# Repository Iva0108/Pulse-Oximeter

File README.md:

A pulse oximeter project that consists of hardware, firmware, and software implementation. This project is provided for educational and research purposes only, 
and is NOT authorized for medical use.
This project presents a portable pulse oximeter capable of measuring blood oxygen saturation (SpO₂) and heart rate (BPM) using the MAX30102
sensor. The measured values are displayed on an OLED screen and transmitted wirelessly to an Android application via an HC-05 Bluetooth module.

Features:
- Measurement of SpO₂ (oxygen saturation)
- Measurement of heart rate (BPM)
- Real-time display on SSD1306 OLED (128×64)
- Wireless Bluetooth communication
- Custom KiCad PCB design
- Android application for data visualization
- Powered by a 3.7 V Li-Po battery with charging circuitry

Building the Project:

Android App
The Android application was developed in Java using Android Studio. 
It connects to the HC-05 module via Bluetooth SPP and displays the received BPM and SpO₂ values in real time.
Expected data format:
BPM:72,SPO2:98
- Open Oximeter_App/PulseOxApp in Android Studio.
- Allow Gradle synchronization.
- Build and run the application.

Firmware
The firmware was developed in the Arduino IDE for the STM32 Blue Pill. 
It uses the MAX30105 library to acquire sensor data, calculate heart rate and oxygen saturation, and transmit the values over Bluetooth.
- Open BT_PulseOximeter.ino in the Arduino IDE.
- Select the STM32 board package (if not already installed, install it via Boards Manager).
- Upload the firmware using ST-Link. It might be necessary to use ST Programmer for flashing instead of doing it directly in Arduino IDE, in which case you will need
to select either a .bin or .elf file to do so.

PCB
The custom PCB was designed in KiCad as a two-layer board with separate schematic sheets for power supply, MCU, sensor module, HC-05 Bluetooth module and OLED display.
- Open Oximeter.kicad_pro in KiCad.
- Use the PCB editor or 3D viewer to inspect the design.

Hardware & Firmware:

Android App:

PCB:

Case:

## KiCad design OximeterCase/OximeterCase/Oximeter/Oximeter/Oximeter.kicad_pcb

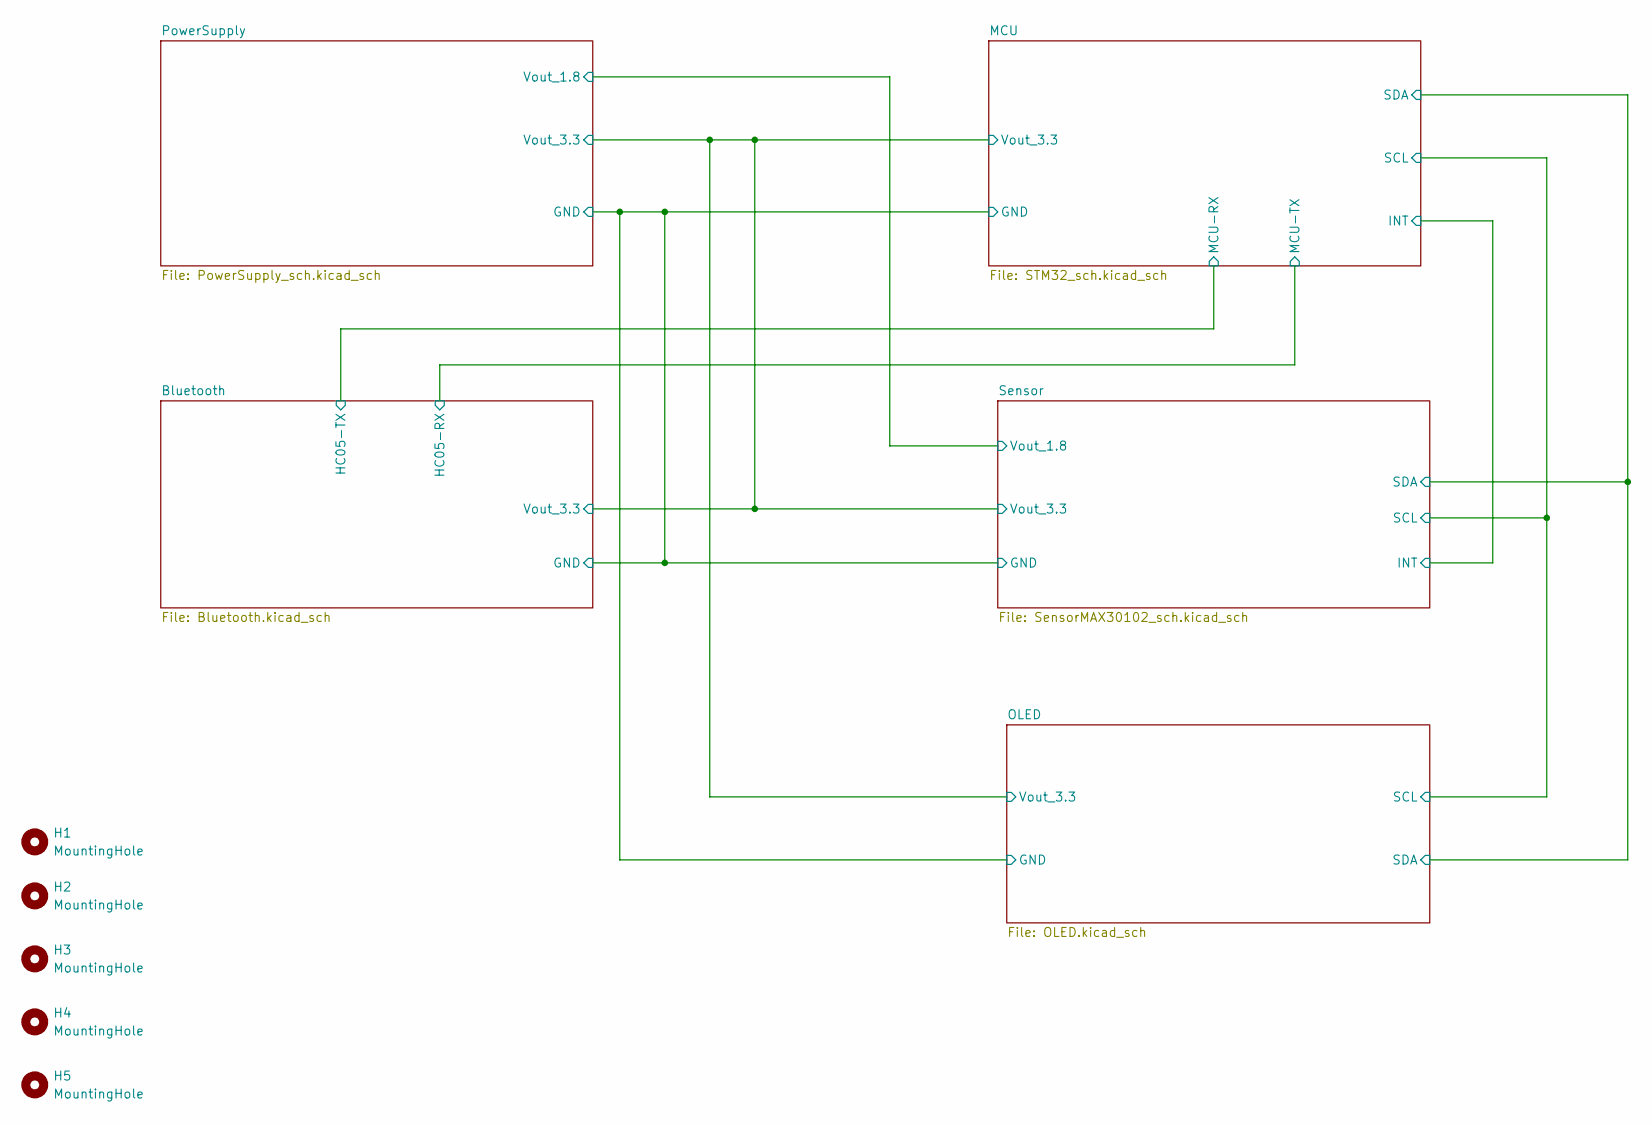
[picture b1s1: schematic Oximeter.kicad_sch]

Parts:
H1, H2, H3, H4, H5: MountingHole; MountingHole_2.2mm_M2

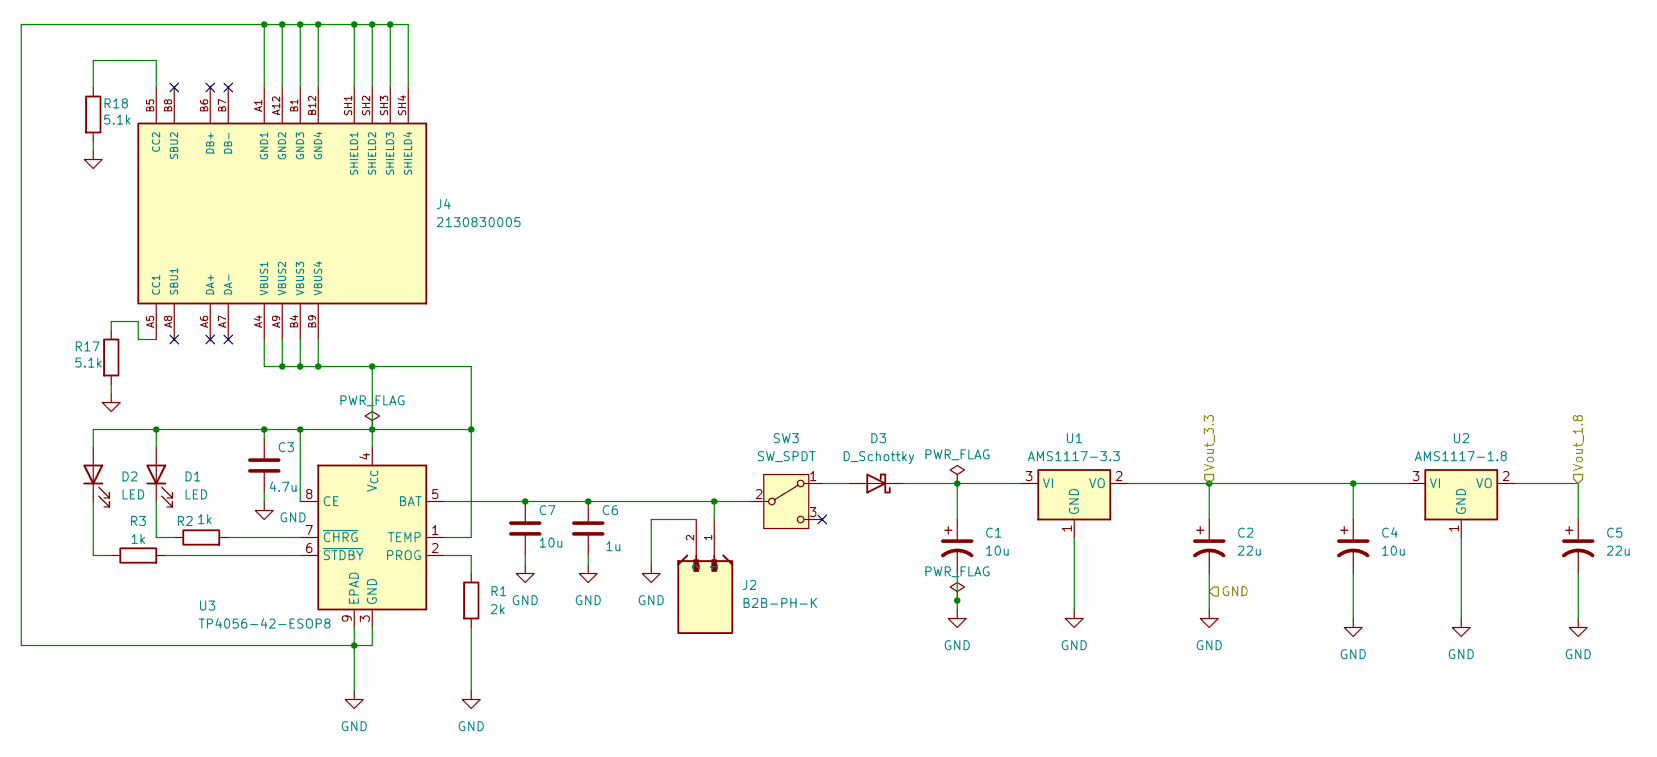
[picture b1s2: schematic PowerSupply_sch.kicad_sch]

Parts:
C1, C4, C7: 10u; C_1206_3216Metric_Pad1.33x1.80mm_HandSolder
C2, C5: 22u; C_1206_3216Metric_Pad1.33x1.80mm_HandSolder
C3: 4.7u; C_1206_3216Metric_Pad1.33x1.80mm_HandSolder
C6: 1u; C_1206_3216Metric_Pad1.33x1.80mm_HandSolder
D1: LED; LED_D3.0mm_Horizontal_O1.27mm_Z2.0mm
D2: LED; LED_D3.0mm_Horizontal_O1.27mm_Z2.0mm_Clear
D3: D_Schottky; D_SMA
J2: B2B-PH-K; JST_B2B-PH-K
J4: 2130830005; MOLEX_2130830005; PARTREV A1
R1: 2k; R_0805_2012Metric
R2, R3: 1k; R_0805_2012Metric
R17, R18: 5.1k; R_0805_2012Metric
SW3: SW_SPDT; SW_E-Switch_EG1224_SPDT_Angled
U1: AMS1117-3.3; SOT-223-3_TabPin2
U2: AMS1117-1.8; SOT-223-3_TabPin2
U3: TP4056-42-ESOP8; SOIC-8-1EP_3.9x4.9mm_P1.27mm_EP2.41x3.3mm_ThermalVias

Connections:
GND: C1.2, C2.2, C3.2, C4.2, C5.2, C6.2, C7.2, J2.2, J4.A1 (GND1), J4.A12 (GND2), J4.B1 (GND3), J4.B12 (GND4), J4.SH1 (SHIELD1), J4.SH2 (SHIELD2), J4.SH3 (SHIELD3), J4.SH4 (SHIELD4), R1.2, R17.2, R18.2, U1.1 (GND), U2.1 (GND), U3.3 (GND), U3.9 (EPAD); also elsewhere on the board
unnamed: C3.1, D1.2 (A), D2.2 (A), J4.A4 (VBUS1), J4.A9 (VBUS2), J4.B4 (VBUS3), J4.B9 (VBUS4), U3.1 (TEMP), U3.4 (V_{CC}), U3.8 (CE)
unnamed: D1.1 (K), R2.1
unnamed: D2.1 (K), R3.1
unnamed: D3.2 (A), SW3.1 (A)
unnamed: C1.1, D3.1 (K), U1.3 (VI)
unnamed: J4.A5 (CC1), R17.1
unnamed: J4.B5 (CC2), R18.1
unnamed: C6.1, C7.1, J2.1, SW3.2 (B), U3.5 (BAT)
unnamed: R1.1, U3.2 (PROG)
unnamed: R2.2, U3.7 (~CHRG)
unnamed: R3.2, U3.6 (~STDBY)
VLED+: C5.1, U2.2 (VO); also elsewhere on the board
Vout_3.3: C2.1, C4.1, U1.2 (VO), U2.3 (VI); also elsewhere on the board

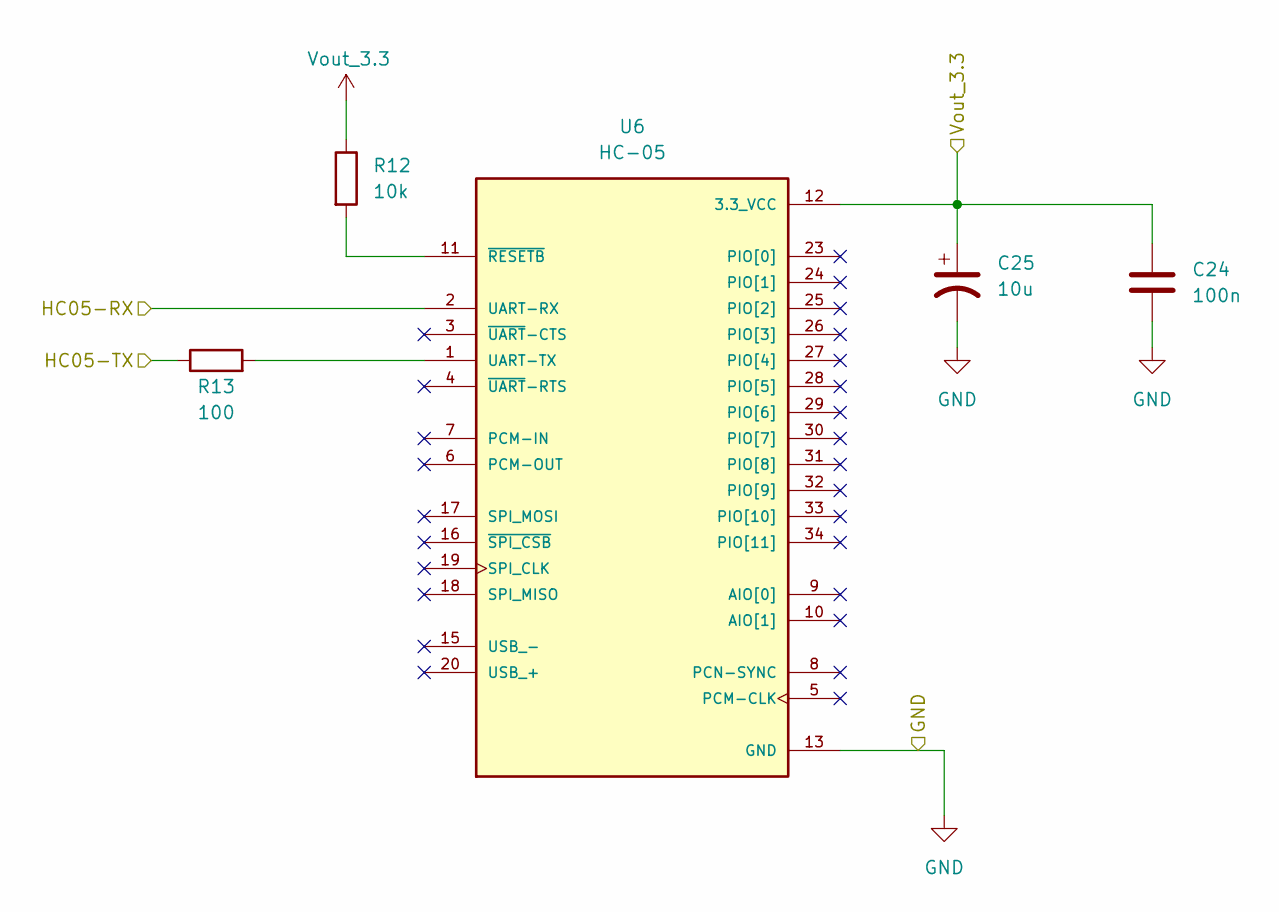
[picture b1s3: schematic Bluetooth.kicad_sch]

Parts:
C24: 100n; C_1206_3216Metric_Pad1.33x1.80mm_HandSolder
C25: 10u; C_1206_3216Metric_Pad1.33x1.80mm_HandSolder
R12: 10k; R_0805_2012Metric
R13: 100; R_0805_2012Metric
U6: HC-05; XCVR_HC-05; PARTREV v1.0

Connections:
/Bluetooth/HC05-RX: U6.2 (UART-RX); also elsewhere on the board
/Bluetooth/HC05-TX: R13.1; also elsewhere on the board
GND: C24.2, C25.2, U6.13 (GND), U6.21 (GND), U6.22 (GND); also elsewhere on the board
unnamed: R13.2, U6.1 (UART-TX)
unnamed: R12.2, U6.11 (~RESETB)
Vout_3.3: C24.1, C25.1, R12.1, U6.12 (3.3_VCC); also elsewhere on the board

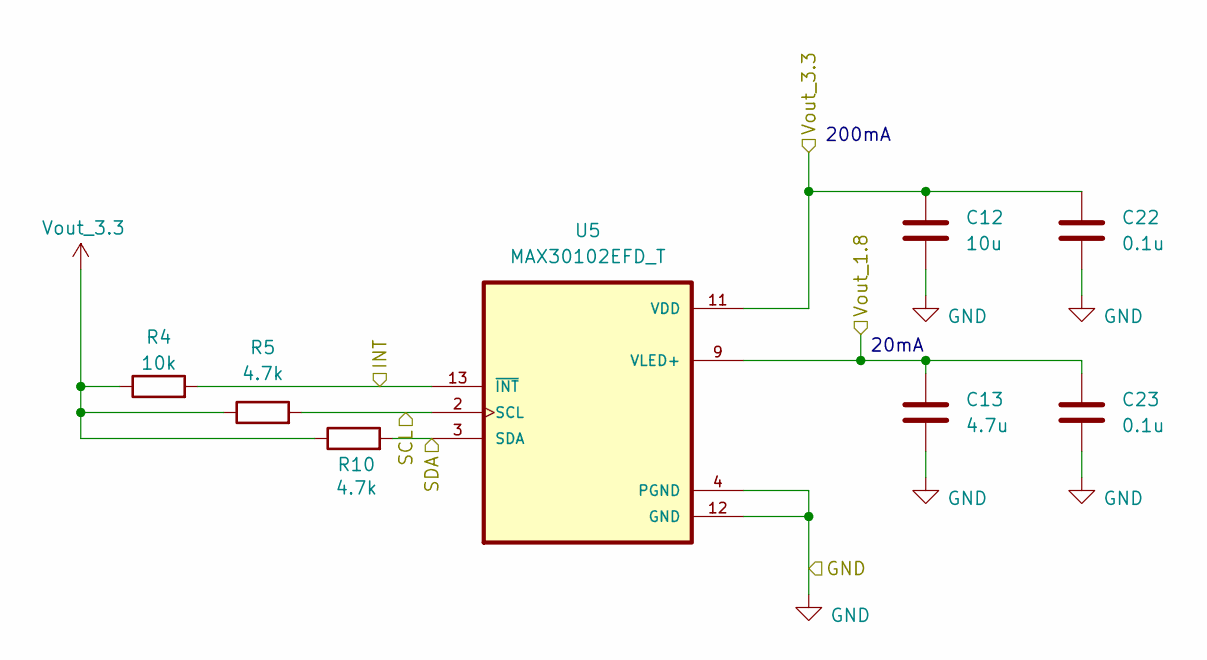
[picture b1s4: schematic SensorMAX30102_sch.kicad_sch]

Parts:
C12: 10u; C_1206_3216Metric_Pad1.33x1.80mm_HandSolder
C13: 4.7u; C_1206_3216Metric_Pad1.33x1.80mm_HandSolder
C22, C23: 0.1u; C_1206_3216Metric_Pad1.33x1.80mm_HandSolder
R4: 10k; R_0805_2012Metric
R5, R10: 4.7k; R_0805_2012Metric
U5: MAX30102EFD_T; XDCR_MAX30101EFD_

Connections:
/MCU/INT: R4.2, U5.13 (~INT); also elsewhere on the board
/MCU/SCL: R5.2, U5.2 (SCL); also elsewhere on the board
/MCU/SDA: R10.2, U5.3 (SDA); also elsewhere on the board
GND: C12.2, C13.2, C22.2, C23.2, U5.4 (PGND), U5.12 (GND); also elsewhere on the board
VLED+: C13.1, C23.1, U5.9 (VLED+), U5.10 (VLED+); also elsewhere on the board
Vout_3.3: C12.1, C22.1, R4.1, R5.1, R10.1, U5.11 (VDD); also elsewhere on the board

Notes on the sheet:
200mA
20mA

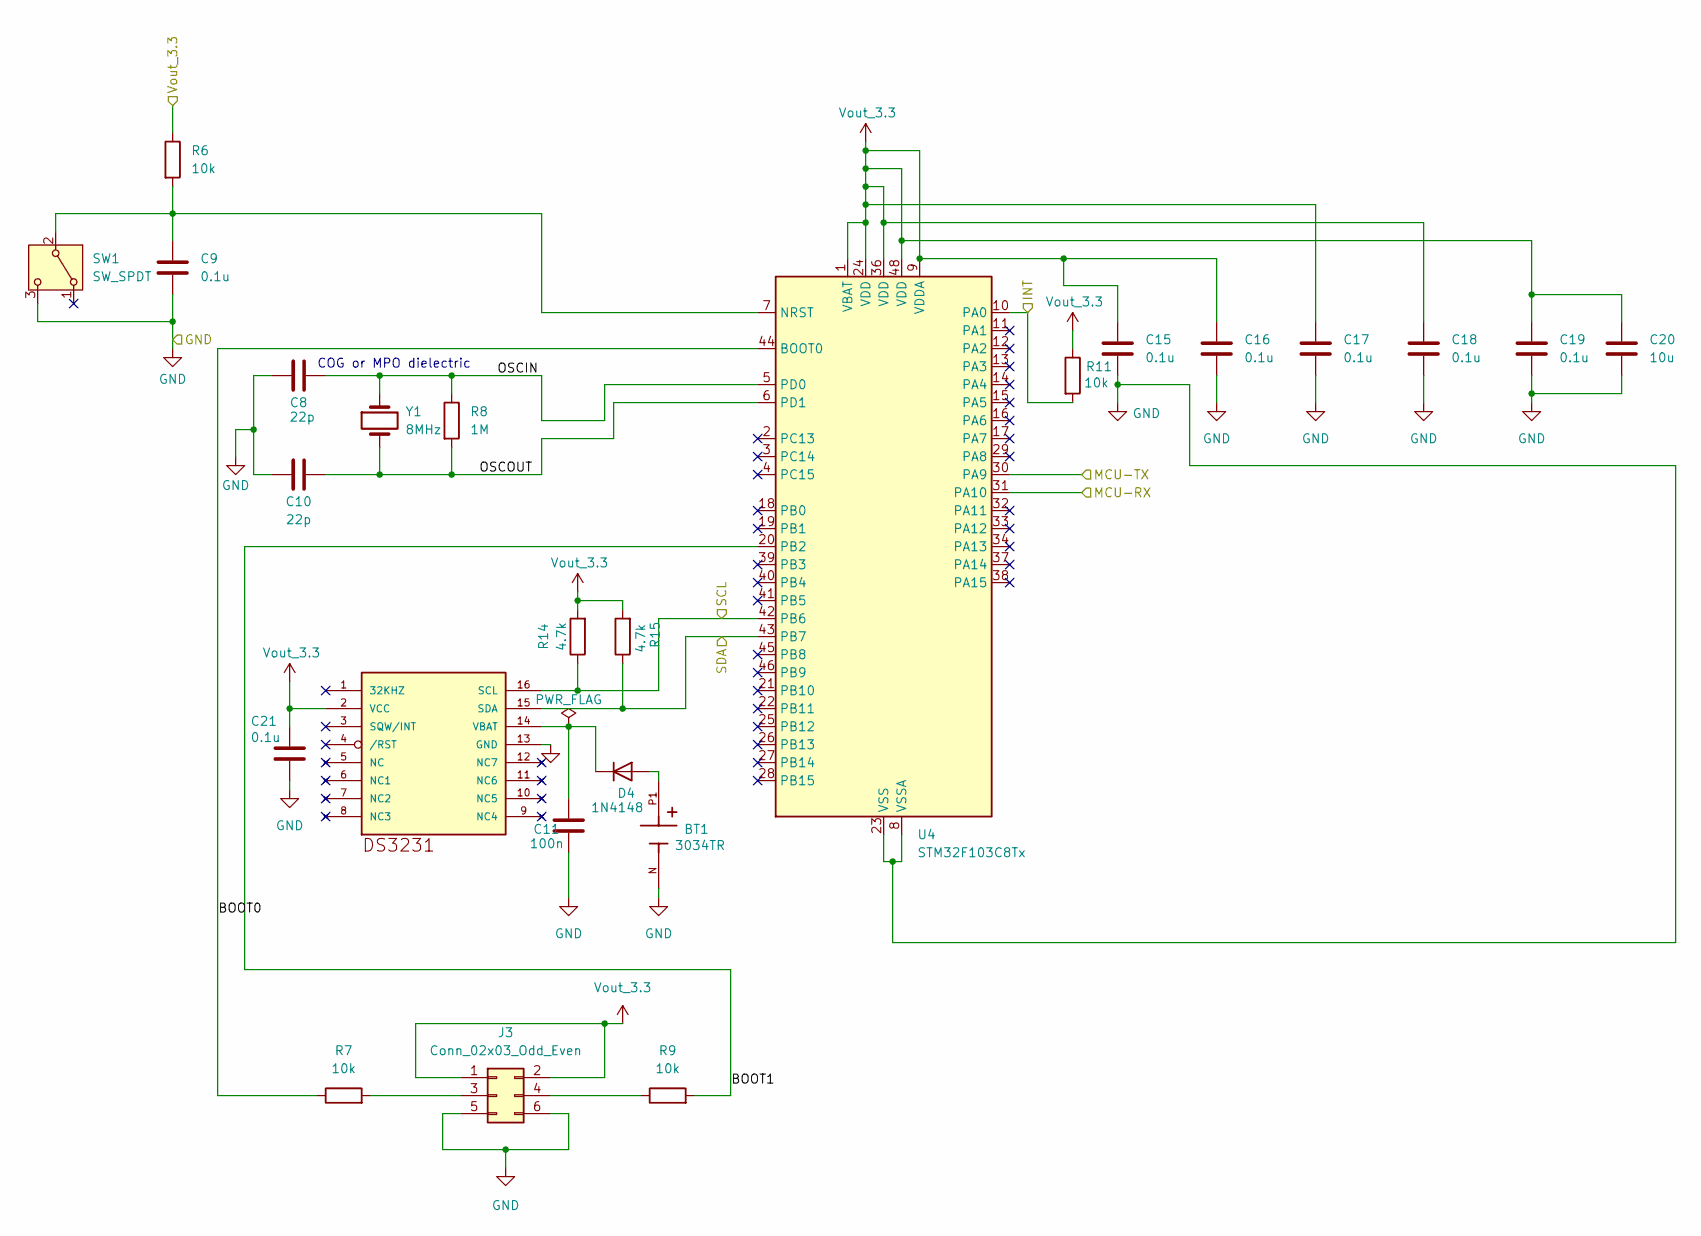
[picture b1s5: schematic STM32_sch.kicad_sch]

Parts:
BT1: 3034TR; BAT_3034TR; PARTREV E
C8, C10: 22p; C_1206_3216Metric_Pad1.33x1.80mm_HandSolder
C9, C15, C16, C17, C18, C19, C21: 0.1u; C_1206_3216Metric_Pad1.33x1.80mm_HandSolder
C11: 100n; C_1206_3216Metric_Pad1.33x1.80mm_HandSolder
C20: 10u; C_1206_3216Metric_Pad1.33x1.80mm_HandSolder
D4: 1N4148; D_DO-35_SOD27_P7.62mm_Horizontal
IC2: DS3231; SO16W
J3: Conn_02x03_Odd_Even; PinHeader_2x03_P2.54mm_Vertical
R6, R7, R9, R11: 10k; R_0805_2012Metric
R8: 1M; R_0805_2012Metric
R14, R15: 4.7k; R_0805_2012Metric
SW1: SW_SPDT; SW_NKK_BB15AH
U4: STM32F103C8Tx; LQFP-48_7x7mm_P0.5mm
Y1: 8MHz; Crystal_SMD_HC49-SD

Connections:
/Bluetooth/HC05-RX: U4.30 (PA9); also elsewhere on the board
/Bluetooth/HC05-TX: U4.31 (PA10); also elsewhere on the board
/MCU/BOOT0: R7.1, U4.44 (BOOT0)
/MCU/BOOT1: R9.2, U4.20 (PB2)
/MCU/INT: R11.2, U4.10 (PA0); also elsewhere on the board
/MCU/OSCIN: C8.2, R8.1, U4.5 (PD0), Y1.1
/MCU/OSCOUT: C10.2, R8.2, U4.6 (PD1), Y1.2
/MCU/SCL: IC2.16 (SCL), R14.1, U4.42 (PB6); also elsewhere on the board
/MCU/SDA: IC2.15 (SDA), R15.1, U4.43 (PB7); also elsewhere on the board
GND: BT1.N, C8.1, C9.2, C10.1, C11.2, C15.2, C16.2, C17.2, C18.2, C19.2, C20.2, C21.2, IC2.13 (GND), J3.5, J3.6, SW1.3 (C), U4.8 (VSSA), U4.23 (VSS), U4.35 (VSS), U4.47 (VSS); also elsewhere on the board
unnamed: BT1.P1, BT1.P2, D4.2 (A)
unnamed: C11.1, D4.1 (K), IC2.14 (VBAT)
unnamed: J3.3, R7.2
unnamed: J3.4, R9.1
unnamed: C9.1, R6.2, SW1.2 (B), U4.7 (NRST)
Vout_3.3: C15.1, C16.1, C17.1, C18.1, C19.1, C20.1, C21.1, IC2.2 (VCC), J3.1, J3.2, R6.1, R11.1, R14.2, R15.2, U4.1 (VBAT), U4.9 (VDDA), U4.24 (VDD), U4.36 (VDD), U4.48 (VDD); also elsewhere on the board

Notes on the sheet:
COG or MPO dielectric

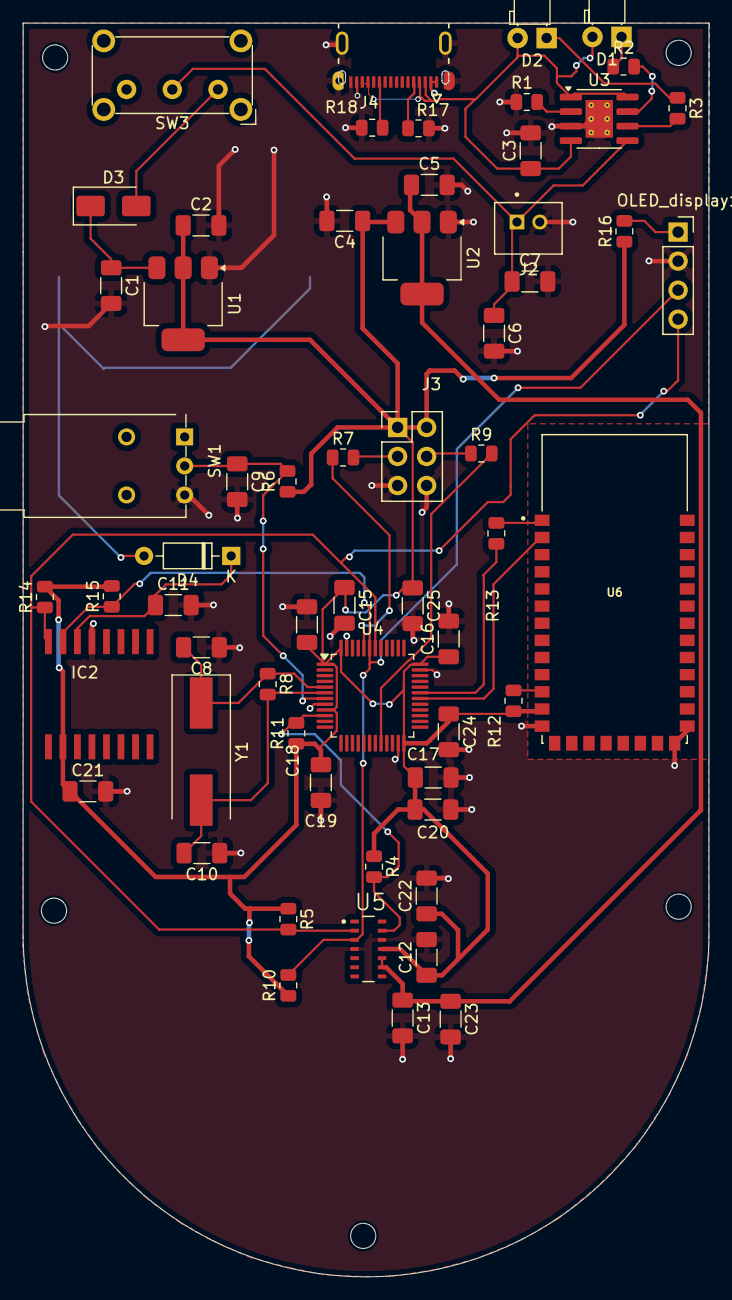
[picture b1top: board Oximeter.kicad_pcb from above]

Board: 2 copper layers, 60.0 x 109.7 mm, 66 parts (1 on the bottom side), 31 nets.

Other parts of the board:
OLED_display1: Conn_01x04_Socket; PinSocket_1x04_P2.54mm_Vertical
R16: 4.7k; R_0805_2012Metric

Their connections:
/MCU/SCL: OLED_display1.4; also elsewhere on the board
/MCU/SDA: OLED_display1.3; also elsewhere on the board
GND: OLED_display1.2; also elsewhere on the board
unnamed: OLED_display1.1, R16.2
Vout_3.3: R16.1; also elsewhere on the board
